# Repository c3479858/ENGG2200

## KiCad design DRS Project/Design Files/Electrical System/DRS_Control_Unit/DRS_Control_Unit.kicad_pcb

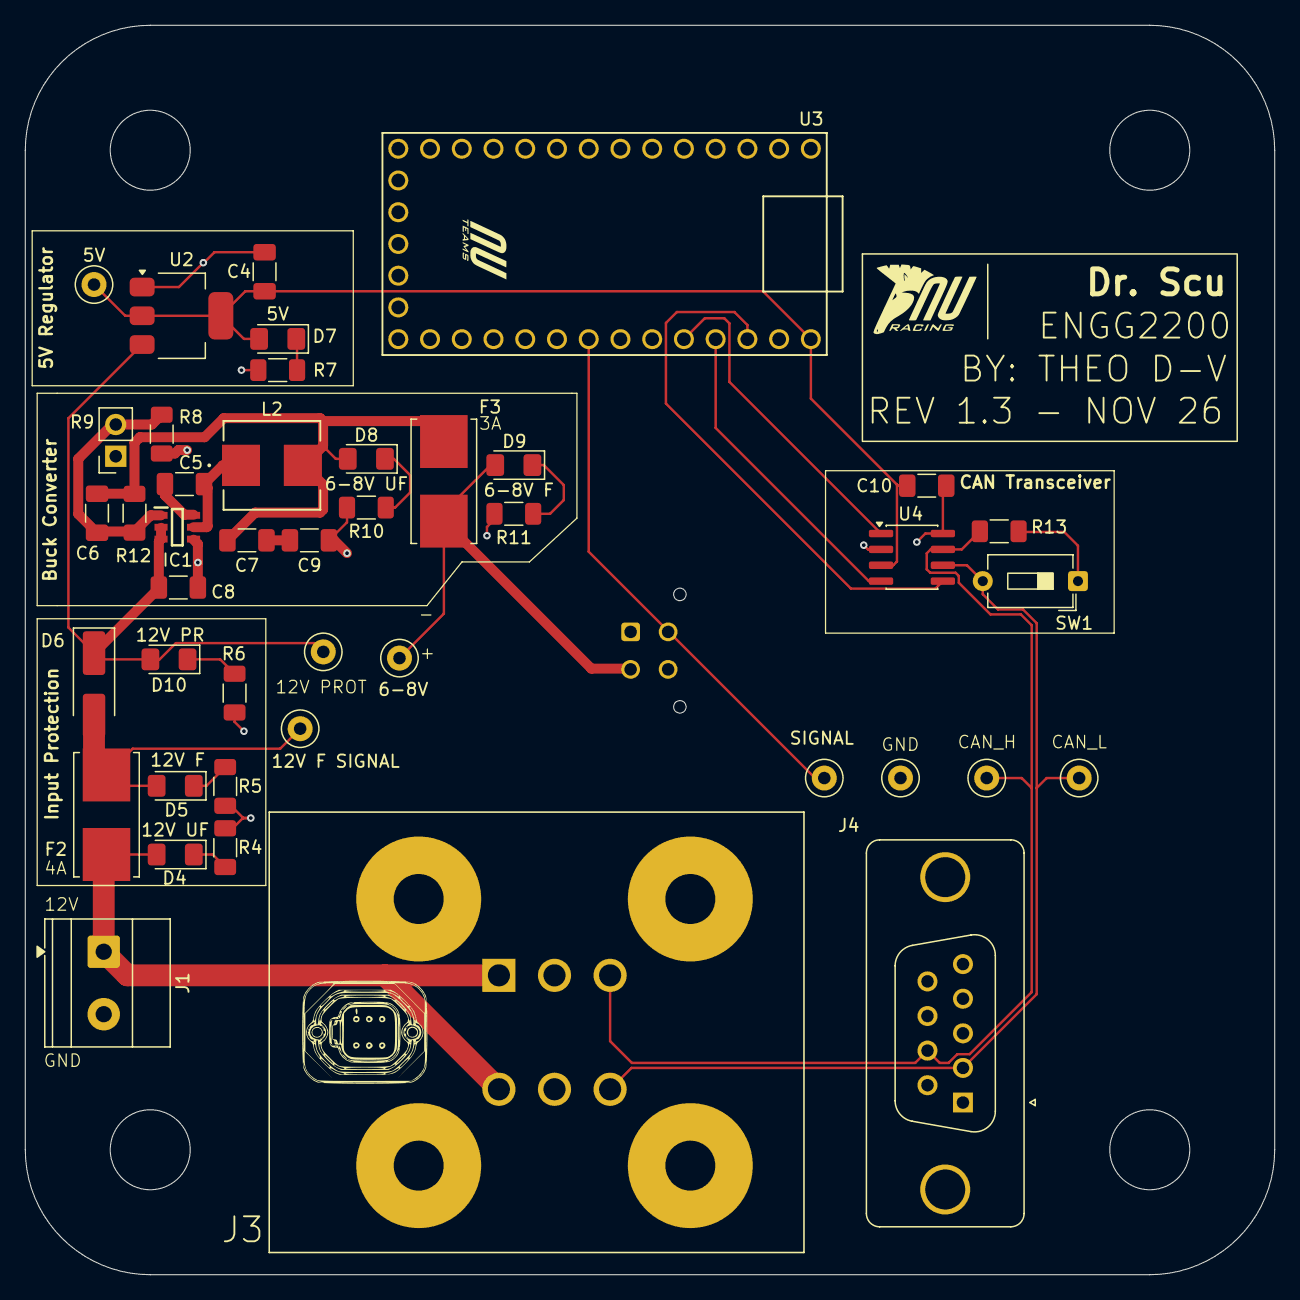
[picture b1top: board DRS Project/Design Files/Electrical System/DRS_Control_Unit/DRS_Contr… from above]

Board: 2 copper layers, 100.0 x 100.0 mm, 49 parts (1 on the bottom side), 24 nets.

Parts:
C4, C7, C9: 22u; C_1206_3216Metric_Pad1.33x1.80mm_HandSolder
C5: 100u; C_1206_3216Metric_Pad1.33x1.80mm_HandSolder
C6: 47p; C_1206_3216Metric_Pad1.33x1.80mm_HandSolder
C8: 10u; C_1206_3216Metric_Pad1.33x1.80mm_HandSolder
C10: 100n; C_1206_3216Metric_Pad1.33x1.80mm_HandSolder
D4: +12V RAW; LED_1206_3216Metric_Pad1.42x1.75mm_HandSolder
D5: +12V FUSED; LED_1206_3216Metric_Pad1.42x1.75mm_HandSolder
D6: SS54; D_SMA_Handsoldering
D7: +5V; LED_1206_3216Metric_Pad1.42x1.75mm_HandSolder
D8: +6-8V RAW; LED_1206_3216Metric_Pad1.42x1.75mm_HandSolder
D9: +6-8V FUSED; LED_1206_3216Metric_Pad1.42x1.75mm_HandSolder
D10: +12V PROT; LED_1206_3216Metric_Pad1.42x1.75mm_HandSolder
F2: 4A; Fuseholder_Littelfuse_Nano2_154x
F3: 3A; Fuseholder_Littelfuse_Nano2_154x
H1, H2, H3, H4: MountingHole_6.4mm_M6
IC1: AP63301QWU-7; SOT95P280X100-6N
J1: Screw; TerminalBlock_Phoenix_MKDS-1,5-2_1x02_P5.00mm_Horizontal
J3: Deutsch DT; DT15-6P
J4: DE-9 Socket; DSUB-9_Socket_Vertical_P2.77x2.84mm_MountingHoles
J5: Servo; microfit-2x02
L2: 10u; IND_ASPI-0630LR_ABR-M
R4, R5, R6: 1.2k; R_1206_3216Metric_Pad1.30x1.75mm_HandSolder
R7: 330R; R_1206_3216Metric_Pad1.30x1.75mm_HandSolder
R8: 9k; R_1206_3216Metric_Pad1.30x1.75mm_HandSolder
R9: SOCKET; PinSocket_1x02_P2.54mm_Vertical
R10, R11: 680R; R_1206_3216Metric_Pad1.30x1.75mm_HandSolder
R12: 1k; R_1206_3216Metric_Pad1.30x1.75mm_HandSolder
R13: 120R; R_1206_3216Metric_Pad1.30x1.75mm_HandSolder
SW1: DSIC01THGET; SW_DIP_SPSTx01_Slide_6.7x4.1mm_W7.62mm_P2.54mm_LowProfile
TP3: +5V Regulated.; TestPoint_Loop_D1.80mm_Drill1.0mm_Beaded
TP4: +12V Fused; TestPoint_Loop_D1.80mm_Drill1.0mm_Beaded
TP5: Ground; TestPoint_Loop_D1.80mm_Drill1.0mm_Beaded
TP6: Servo Signal; TestPoint_Loop_D1.80mm_Drill1.0mm_Beaded
TP7: +6-8V REGULATED; TestPoint_Loop_D1.80mm_Drill1.0mm_Beaded
TP8: CAN_H1; TestPoint_Loop_D1.80mm_Drill1.0mm_Beaded
TP9: CAN_L1; TestPoint_Loop_D1.80mm_Drill1.0mm_Beaded
TP10: +12V Protected; TestPoint_Loop_D1.80mm_Drill1.0mm_Beaded
U2: AMS1117; SOT-223-3_TabPin2
U3: Teensy4.0-NU-Teams
U4: TJA1051T-3; SOIC-8_3.9x4.9mm_P1.27mm
U5: BRANDING_RACING

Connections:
+3.3V: U3.3V3R (3V3), U4.5 (VIO)
+5V: C4.1, C10.1, D7.2 (A), TP3.1 (1_1), U2.2 (VO), U3.VIN, U4.3 (VCC)
+6-8V: D9.2 (A), F3.2, J5.2, TP7.1 (1_1)
+12V: D4.2 (A), F2.1, J1.1, J3.1, J3.6
/CAN HIGH: J3.3, J4.7, R13.1, TP8.1 (1_1), U4.7 (CANH)
/CAN LOW: J3.4, J4.2, SW1.2, TP9.1 (1_1), U4.6 (CANL)
/RX: U3.23 (23_CAN1_RX), U4.4 (RXD)
/SIGNAL: J5.3, TP6.1 (1_1), U3.19 (19_A5_SCL0)
/TX: U3.22 (22_CAN1_TX), U4.1 (TXD)
/VIN: C8.1, D6.1 (K), D10.2 (A), IC1.2 (EN), IC1.3 (VIN), TP10.1 (1_1), U2.3 (VI)
GND: C4.2, C8.2, C9.2, C10.2, IC1.4 (GND), J1.2, J3.2, J3.5, J5.1, R4.2, R5.2, R6.2, R7.1, R8.1, R9.1, R10.1, R11.2, TP5.1 (1_1), U2.1 (ADJ), U3.GNDB (GND), U3.GNDL (GND), U3.GNDR (GND), U4.2 (GND), U4.8 (S)
unnamed: C7.2, C9.1
unnamed: D4.1 (K), R4.1
unnamed: D5.2 (A), D6.2 (A), F2.2, TP4.1 (1_1)
unnamed: D5.1 (K), R5.1
unnamed: D7.1 (K), R7.2
unnamed: C6.2, C7.1, D8.2 (A), F3.1, L2.2, R12.2
unnamed: D8.1 (K), R10.2
unnamed: D9.1 (K), R11.1
unnamed: D10.1 (K), R6.1
unnamed: C5.1, IC1.6 (BST)
unnamed: C6.1, IC1.1 (FB), R8.2, R9.2, R12.1
unnamed: C5.2, IC1.5 (SW), L2.1
unnamed: R13.2, SW1.1

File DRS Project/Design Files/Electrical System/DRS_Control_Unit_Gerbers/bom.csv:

Designator,Footprint,Quantity,Value,LCSC Part #
C10,1206,1,100n,
"C4, C7, C9",1206,3,22u,
C5,1206,1,100u,
C6,1206,1,47p,
C8,1206,1,10u,
D10,1206,1,+12V PR,
D4,1206,1,+12V U.F.,
D5,1206,1,+12V F,
D6,D_SMA_Handsoldering,1,SS54,
D7,1206,1,+5V,
D8,1206,1,+(VAR)V U.F.,
D9,1206,1,+(VAR)V F,
F2,Fuseholder_Littelfuse_Nano2_154x,1,4A,
F3,Fuseholder_Littelfuse_Nano2_154x,1,3A,
IC1,SOT95P280X100-6N,1,AP63301QWU-7,
J1,"TerminalBlock_Phoenix_MKDS-1,5-2_1x02_P5.00mm_Horizontal",1,Screw,
J2,PinHeader_1x03_P2.54mm_Vertical,1,Servo,
J3,DT15-6P,1,Deutsch DT,
J4,DSUB-9_Socket_Vertical_P2.77x2.84mm_MountingHoles,1,DE-9 Socket,
L2,IND_ASPI-0630LR_ABR-M,1,10u,
"R10, R11",1206,2,680R,
R12,1206,1,1k,
R13,1206,1,120,
"R4, R5, R6",1206,3,1.2k,
R7,1206,1,330R,
R8,1206,1,9k,
R9,PinSocket_1x02_P2.54mm_Vertical,1,SOCKET,
SW1,SW_DIP_SPSTx01_Slide_6.7x4.1mm_W7.62mm_P2.54mm_LowProfile,1,DSIC01THGET,
TP3,TestPoint_Loop_D1.80mm_Drill1.0mm_Beaded,1,+5V Regulated.,
TP4,TestPoint_Loop_D1.80mm_Drill1.0mm_Beaded,1,+12V Fused,
TP5,TestPoint_Loop_D1.80mm_Drill1.0mm_Beaded,1,Ground,
TP6,TestPoint_Loop_D1.80mm_Drill1.0mm_Beaded,1,Servo Signal,
TP7,TestPoint_Loop_D1.80mm_Drill1.0mm_Beaded,1,+(VAR)V Regulated,
TP8,TestPoint_Loop_D1.80mm_Drill1.0mm_Beaded,1,CAN_H1,
TP9,TestPoint_Loop_D1.80mm_Drill1.0mm_Beaded,1,CAN_L1,
U2,SOT-223-3_TabPin2,1,AMS1117,
U3,Teensy4.0-NU-Teams,1,Teensy4.0-NU-Teams,
U4,SOIC-8_3.9x4.9mm_P1.27mm,1,TJA1051T-3,
U5,BRANDING_RACING,1,~,

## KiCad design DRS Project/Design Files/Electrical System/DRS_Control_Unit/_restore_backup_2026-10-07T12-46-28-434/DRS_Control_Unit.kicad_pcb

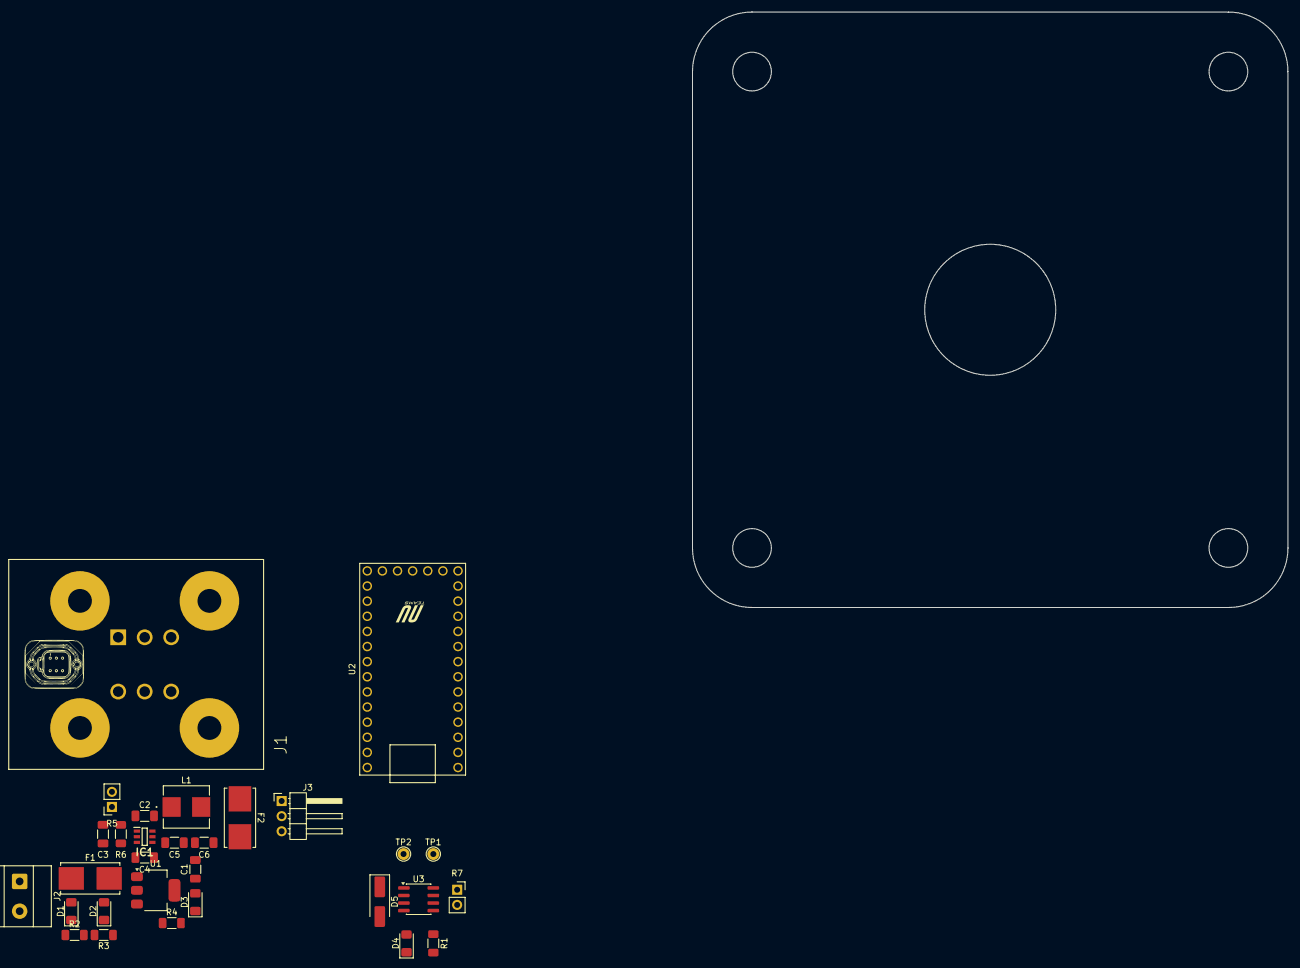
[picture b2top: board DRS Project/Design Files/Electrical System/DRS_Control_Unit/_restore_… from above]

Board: 2 copper layers, 100.0 x 100.0 mm, 30 parts (0 on the bottom side), 21 nets, no tracks yet.

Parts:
C1, C5, C6: 22u; C_1206_3216Metric_Pad1.33x1.80mm_HandSolder
C2: 100u; C_1206_3216Metric_Pad1.33x1.80mm_HandSolder
C3: C4; C_1206_3216Metric_Pad1.33x1.80mm_HandSolder
C4: 10u; C_1206_3216Metric_Pad1.33x1.80mm_HandSolder
D1: +12V U.F.; LED_1206_3216Metric_Pad1.42x1.75mm_HandSolder
D2: +12V F; LED_1206_3216Metric_Pad1.42x1.75mm_HandSolder
D3: +5V; LED_1206_3216Metric_Pad1.42x1.75mm_HandSolder
D4: +5V PROT; LED_1206_3216Metric_Pad1.42x1.75mm_HandSolder
D5: SS34; D_SMA_Handsoldering
F1: 5A; Fuseholder_Littelfuse_Nano2_154x
F2: 3A; Fuseholder_Littelfuse_Nano2_154x
IC1: AP63301QWU-7; SOT95P280X100-6N
J1: Deutsch DT; DT15-6P
J2: Screw; TerminalBlock_Phoenix_MKDS-1,5-2_1x02_P5.00mm_Horizontal
J3: Servo; PinHeader_1x03_P2.54mm_Horizontal
L1: 4.7u; IND_ASPI-0630LR_ABR-M
R1, R4: 330R; R_1206_3216Metric_Pad1.30x1.75mm_HandSolder
R2, R3: 1.2k; R_1206_3216Metric_Pad1.30x1.75mm_HandSolder
R5: 9k; PinSocket_1x02_P2.54mm_Vertical
R6: 1k; R_1206_3216Metric_Pad1.30x1.75mm_HandSolder
R7: R; PinSocket_1x02_P2.54mm_Vertical
TP1: CANH; TestPoint_THTPad_D2.0mm_Drill1.0mm
TP2: CANL; TestPoint_THTPad_D2.0mm_Drill1.0mm
U1: AMS1117; SOT-223-3_TabPin2
U2: Teensy4.0-NU-Teams
U3: TJA1051T-3; SOIC-8_3.9x4.9mm_P1.27mm

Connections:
+5V: C1.1, D3.2 (A), D5.2 (A), U1.2 (VO)
+6V: F2.2, J3.2
+12V: D1.2 (A), F1.1, J1.1, J1.6, J2.1
/CAN HIGH: J1.4, R7.1, TP1.1 (1_1), U3.7 (CANH)
/CAN LOW: J1.3, R7.2, TP2.1 (1_1), U3.6 (CANL)
/FB: C3.1, IC1.1 (FB), R5.2, R6.1
/SIGNAL: J3.3, U2.19 (19_A5_SCL0)
/VIN: C4.1, D2.2 (A), F1.2, IC1.2 (EN), IC1.3 (VIN), U1.3 (VI)
GND: C1.2, C4.2, C6.2, IC1.4 (GND), J1.2, J1.5, J2.2, J3.1, R1.1, R2.2, R3.2, R4.1, R5.1, U1.1 (ADJ), U2.GNDB (GND), U2.GNDL (GND), U2.GNDR (GND), U3.2 (GND), U3.8 (S)
unnamed: C3.2, C5.1, F2.1, L1.2, R6.2
unnamed: C5.2, C6.1
unnamed: D1.1 (K), R2.1
unnamed: D2.1 (K), R3.1
unnamed: D3.1 (K), R4.2
unnamed: D4.2 (A), D5.1 (K), U3.3 (VCC)
unnamed: D4.1 (K), R1.2
unnamed: C2.1, IC1.6 (BST)
unnamed: C2.2, IC1.5 (SW), L1.1
unnamed: U2.22 (22_CAN1_TX), U3.1 (TXD)
unnamed: U2.23 (23_CAN1_RX), U3.4 (RXD)
unnamed: U2.VIN, U3.5 (VIO)

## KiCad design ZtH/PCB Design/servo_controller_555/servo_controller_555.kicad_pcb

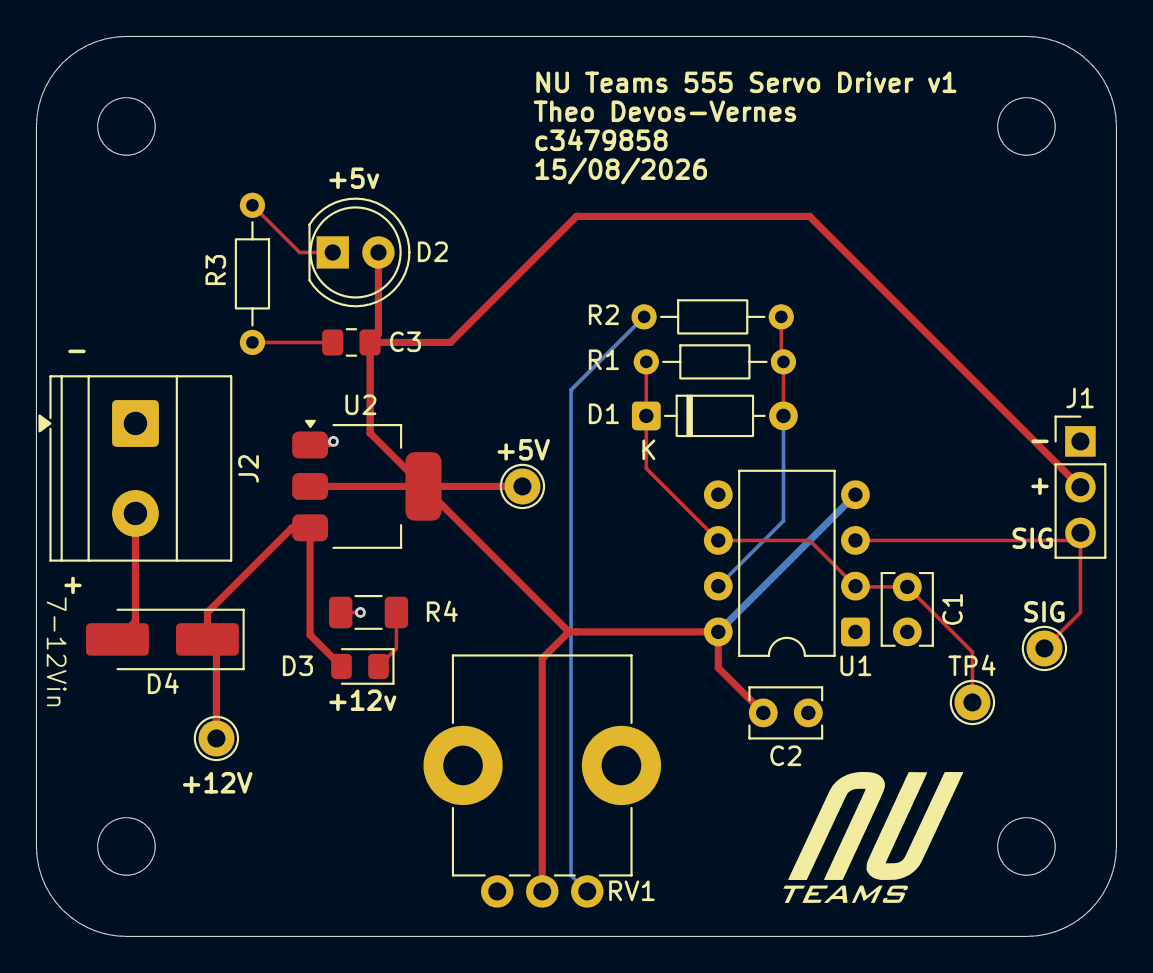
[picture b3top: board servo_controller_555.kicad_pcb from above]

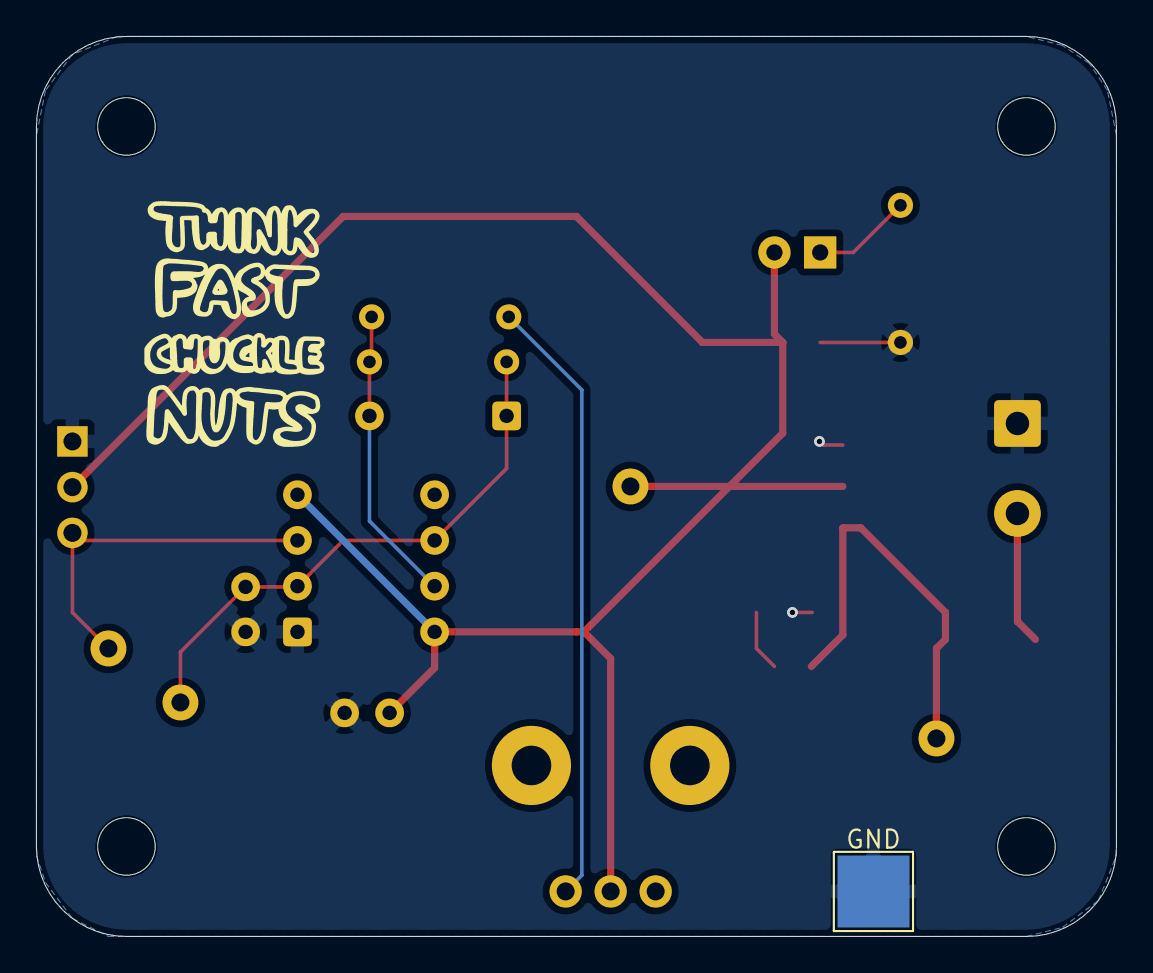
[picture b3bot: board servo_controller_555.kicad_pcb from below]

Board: 2 copper layers, 60.0 x 50.0 mm, 22 parts (2 on the bottom side), 10 nets.

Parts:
+5V, +12V: TestPoint; TestPoint_THTPad_D2.0mm_Drill1.0mm
C1: 22n; C_Disc_D3.8mm_W2.6mm_P2.50mm
C2: 100n; C_Disc_D3.8mm_W2.6mm_P2.50mm
C3: 22u; C_0805_2012Metric_Pad1.18x1.45mm_HandSolder
D1: 1N4148; D_DO-35_SOD27_P7.62mm_Horizontal
D2: LED; LED_D5.0mm
D3: LED; LED_0805_2012Metric_Pad1.15x1.40mm_HandSolder
D4: D; D_SMA_Handsoldering
GND: TestPoint; TestPoint_Pad_4.0x4.0mm
J1: SERVO; PinHeader_1x03_P2.54mm_Vertical
J2: VIN; TerminalBlock_Phoenix_MKDS-1,5-2_1x02_P5.00mm_Horizontal
R1: 1M; R_Axial_DIN0204_L3.6mm_D1.6mm_P7.62mm_Horizontal
R2: 22k; R_Axial_DIN0204_L3.6mm_D1.6mm_P7.62mm_Horizontal
R3: 1k; R_Axial_DIN0204_L3.6mm_D1.6mm_P7.62mm_Horizontal
R4: 1k; R_1206_3216Metric_Pad1.30x1.75mm_HandSolder
RV1: 100k; Potentiometer_Bourns_PTV09A-1_Single_Vertical
SIG: TestPoint; TestPoint_THTPad_D2.0mm_Drill1.0mm
TP4: TestPoint; TestPoint_THTPad_D2.0mm_Drill1.0mm
ThinkFast: LOGO
U1: LM555xN; DIP-8_W7.62mm
U2: AMS1117; SOT-223-3_TabPin2

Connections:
+5V: +5V.1 (1_1), C2.1, C3.1, D2.2 (A), J1.2, RV1.2, U1.4 (~RST), U1.8 (VCC), U2.2 (VO)
+12V: +12V.1 (1_1), D3.2 (A), D4.1 (K), U2.3 (VI)
GND: C1.2, C2.2, C3.2, GND.1 (1_1), J1.1, J2.1, R3.2, R4.2, U1.1 (GND), U2.1 (ADJ)
unnamed: D1.2 (A), R1.2, R2.2, U1.7 (DISCH)
unnamed: C1.1, D1.1 (K), R1.1, TP4.1 (1_1), U1.2 (TRIG), U1.6 (THRES)
unnamed: D2.1 (K), R3.1
unnamed: D3.1 (K), R4.1
unnamed: D4.2 (A), J2.2
unnamed: J1.3, SIG.1 (1_1), U1.3 (OUT)
unnamed: R2.1, RV1.1
